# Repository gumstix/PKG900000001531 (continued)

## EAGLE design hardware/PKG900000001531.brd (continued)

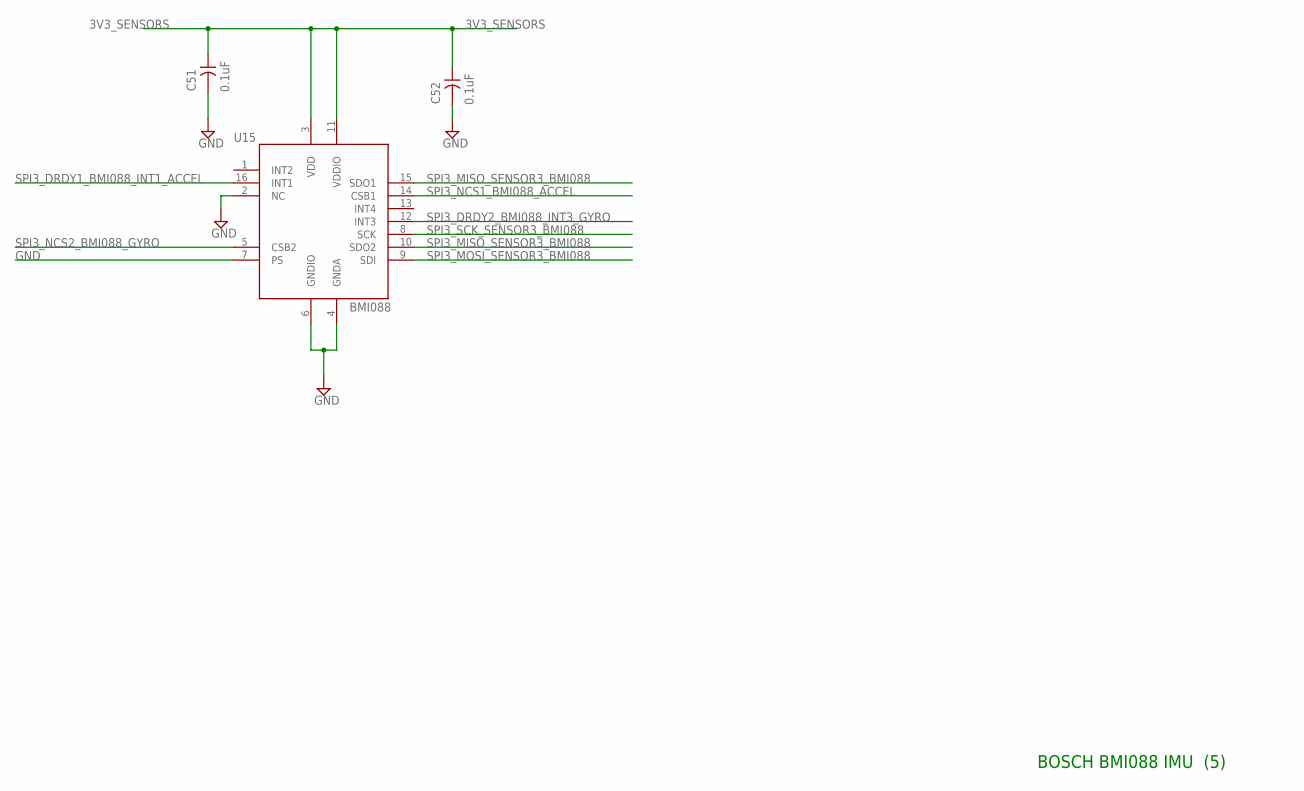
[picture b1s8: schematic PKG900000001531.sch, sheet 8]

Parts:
C51, C52: 0.1uF; 0201
U15: BMI088; LGA16-BMI088

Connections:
3V3_SENSORS: C51.1, C52.1, U15.3 (VDD), U15.11 (VDDIO); also elsewhere on the board
GND: C51.2, C52.2, U15.2 (NC), U15.4 (GNDA), U15.6 (GNDIO), U15.7 (PS); also elsewhere on the board
SPI3_DRDY1_BMI088_INT1_ACCEL: U15.16 (INT1); also elsewhere on the board
SPI3_DRDY2_BMI088_INT3_GYRO: U15.12 (INT3); also elsewhere on the board
SPI3_MISO_SENSOR3_BMI088: U15.10 (SDO2), U15.15 (SDO1); also elsewhere on the board
SPI3_MOSI_SENSOR3_BMI088: U15.9 (SDI); also elsewhere on the board
SPI3_NCS1_BMI088_ACCEL: U15.14 (CSB1); also elsewhere on the board
SPI3_NCS2_BMI088_GYRO: U15.5 (CSB2); also elsewhere on the board
SPI3_SCK_SENSOR3_BMI088: U15.8 (SCK); also elsewhere on the board

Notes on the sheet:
BOSCH BMI088 IMU (5)

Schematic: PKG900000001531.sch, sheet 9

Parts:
C53, C55: 0.1uF; 0201
R13, R47, R77: 10K 1%; 0201
R17, R46, R86, R87, R88: DNP; 0201
R90, R107: 0R; 0201
R108, R109: 1K5; 0201
U9: BMM150; WLCSP-12

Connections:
3V3_SENSORS: C53.1, C55.1, R47.2, R108.1, R109.1, U9.B2 (VDDIO), U9.E5 (VDD); also elsewhere on the board
BMM150_PS: R46.2, R47.1, U9.A1 (PS)
CSB$1: R77.2, R87.2, U9.A5 (CSB)
GND: C53.2, C55.2, R13.1, R46.1, R77.1, U9.C5 (GND), U9.E1 (GND), U9.E3 (GND); also elsewhere on the board
I2C4_SCL_FMU: R107.2, R109.2; also elsewhere on the board
I2C4_SDA_FMU: R90.2, R108.2; also elsewhere on the board
SCK$1: R17.1, R107.1, U9.A3 (SCK)
SDI$1: R88.1, R90.1, U9.B4 (SDI)
SDO$1: R13.2, R86.2, U9.C1 (SDO)
SPI4_DRDY1_BMM150_DRDY: U9.D4 (DRDY); also elsewhere on the board
SPI4_MISO_SENSOR4_BMM150: R86.1; also elsewhere on the board
SPI4_MOSI_SENSOR4_BMM150: R88.2; also elsewhere on the board
SPI4_NCS1_BMM150: R87.1; also elsewhere on the board
SPI4_SCK_SENSOR4_BMM150: R17.2; also elsewhere on the board

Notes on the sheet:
Bosch BMM150 Magnetometer (6)

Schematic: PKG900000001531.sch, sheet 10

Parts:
C54: DNP; 0201
C70, C71: 0.1uF; 0201
R51, R53, R57, R59: DNP; 0201
U10: DNP; BA03
U108: BMP388; LGA10

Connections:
3V3_SENSORS: C54.1, C70.1, C71.1, R53.1, R57.1, R59.2, U10.1 (VDD), U108.1 (VDDIO), U108.6 (CSB), U108.10 (VDD); also elsewhere on the board
GND: C54.2, C70.2, C71.2, R51.1, U10.3 (GND), U108.3 (VSS), U108.5 (SDO), U108.8 (VSS), U108.9 (VSS); also elsewhere on the board
I2C2_DRDY1_BMP388: U108.7 (INT); also elsewhere on the board
I2C3_SCL_BASE_MS5611_BARBED_EXTERNAL1: R57.2, U10.8 (SCLK); also elsewhere on the board
I2C3_SDA_BASE_MS5611_BARBED_EXTERNAL1: R53.2, U10.7 (SDA); also elsewhere on the board
I2C4_SCL_FMU: U108.2 (SCK); also elsewhere on the board
I2C4_SDA_FMU: U108.4 (SDI); also elsewhere on the board
MS5611_CS$1: R51.2, U10.4 (CSB)
MS5611_PS$1: R59.1, U10.2 (PS)

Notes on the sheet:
BMP388 & MS5611 Barometer (7)

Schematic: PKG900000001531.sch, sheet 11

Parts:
D2: EAST1616RGBB4; SMD4
R78: 196R; 0201
R79, R85: 100R; 0201

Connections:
2.3.3V_VCC_3.3: D2.4 (VCC); also elsewhere on the board
C_BLUE$1: D2.3 (B), R85.1
C_GREEN$1: D2.2 (G), R79.1
C_RED$1: D2.1 (R), R78.1
NLED_BLUE: R85.2; also elsewhere on the board
NLED_GREEN: R79.2; also elsewhere on the board
NLED_RED: R78.2; also elsewhere on the board

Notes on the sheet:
Discrete RGB LED (16)

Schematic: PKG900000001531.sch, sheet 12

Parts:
C228: 0.1uF / 16V; 0402
C230: 10uF / 16V; 0805
C231: 1.0uF; 0402
C232: 10pF; 0201
C233: 22uF; 0805
IC3: TPS62111; PQFP16
L1: 6.8uH; 1515
R80: 1M0; 0201
R81: 0R; 0402
R83: DNP; 0402

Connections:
2.3.3V_VCC_3.3: C232.1, C233.1, L1.2, R80.2, R81.2; also elsewhere on the board
14.5.0V_VCC_5.0: C228.1, C230.1, C231.1, IC3.2 (VIN), IC3.3 (VIN), IC3.4 (EN), IC3.8 (VIN); also elsewhere on the board
FB_3.3$2: C232.2, IC3.10 (FB), R81.1, R83.2
GND: C228.2, C230.2, C231.2, C233.2, IC3.1 (PGND), IC3.5 (SYNC), IC3.6 (LBO), IC3.7 (LBI), IC3.9 (GND), IC3.11 (GND), IC3.12 (GND), IC3.16 (PGND), IC3.P$1 (GND), R83.1; also elsewhere on the board
PG_3.3$2: IC3.13 (PG), R80.1
SW_3.3$2: IC3.14 (SW), IC3.15 (SW), L1.1

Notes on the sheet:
3.3V 1500mA Buck

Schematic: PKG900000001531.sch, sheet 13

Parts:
C226: 1.0uF; 0402
J7: USB-TYPE-C; USB-TYPE-C-SMT
L9: DLP11SN900HL2; 0504-DLP11S
R68, R89: 5K1; 0201
R82: 0R; 0201
U107: TPD4E02B0410-USON; UFDFN-10

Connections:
3.5.0V_VCC_5.0: C226.1, J7.A4 (VBUS), J7.A9 (VBUS), J7.B4 (VBUS), J7.B9 (VBUS), R82.2, U107.5 (P4), U107.6 (P4); also elsewhere on the board
4.USB_D_N: L9.3; also elsewhere on the board
4.USB_D_P: L9.2; also elsewhere on the board
CC1$3: J7.A5 (CC1), R68.2
CC2$3: J7.B5 (CC2), R89.2
COMMON_SHIELD: J7.P$1 (SHIELD), J7.P$2 (SHIELD), J7.P$3 (SHIELD), J7.P$4 (SHIELD), U107.3 (SHIELD), U107.8 (SHIELD)
D_N$3: J7.A7 (D-), J7.B7 (D-), L9.4, U107.1, U107.10 (P1)
D_P$3: J7.A6 (D+), J7.B6 (D+), L9.1, U107.2, U107.9 (P2)
GND: C226.2, J7.A1 (GND), J7.A12 (GND), J7.B1 (GND), J7.B12 (GND), R68.1, R89.1; also elsewhere on the board
RX1_N$3: J7.B10 (RX1-)
RX1_P$3: J7.B11 (RX1+)
RX2_N$3: J7.A10 (RX2-)
RX2_P$3: J7.A11 (RX2+)
TX1_N$3: J7.A3 (TX1-)
TX1_P$3: J7.A2 (TX1+)
TX2_N$3: J7.B3 (TX2-)
TX2_P$3: J7.B2 (TX2+)
VBUS_SENSE: R82.1; also elsewhere on the board

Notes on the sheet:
USB Type-C PD (5V)
Pull both CC pins low with 5.1K 1% to enable UFP and PD.

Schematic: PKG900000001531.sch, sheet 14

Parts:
C7, C13, C95, C97, C238, C239, C240, C241, C248: 0.1uF; 0201
C8, C31, C96: 1.0uF; 0402
C9: 4.7uF; 0603
C10, C11: 22pF; 0201
C12: 0.1uF; 0402
R5, R91, R92, R93, R97, R98, R99: 100K 1%; 0201
R96: 1M0; 0201
R102: 12K0; 0201
U14: USB2517-JZX; QFN64-9X9MM-FT2232HQ
Y1: 24.000MHz; CRYSTAL-3225

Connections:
1.USB_HS_D_N: U14.1 (USBDN1_DM/PRT_DIS_M1); also elsewhere on the board
1.USB_HS_D_P: U14.2 (USBDN1_DP/PRT_DIS_P1); also elsewhere on the board
2.3.3V_VCC_3.3: C7.1, C8.1, C9.1, C13.1, C238.1, C239.1, C240.1, C241.1, C248.1, R5.1, R91.1, R97.1, R98.2, U14.5 (VDDA33_2), U14.10 (VDDA33_4), U14.24 (VDD33CR), U14.46 (VDD33), U14.52 (VDDA33_3), U14.57 (VDDA33), U14.64 (VDD33PLL); also elsewhere on the board
4.USB_D_N: U14.58 (USBUP_DM); also elsewhere on the board
4.USB_D_P: U14.59 (USBUP_DP); also elsewhere on the board
5.USB_DEVICE_D_N: U14.53 (USBDN6_DM/PRT_DIS_M6); also elsewhere on the board
5.USB_DEVICE_D_P: U14.54 (USBDN6_DP/PRT_DIS_P6); also elsewhere on the board
6.USB_DEVICE_D_N: U14.55 (USBDN7_DM/PRT_DIS_M7); also elsewhere on the board
6.USB_DEVICE_D_P: U14.56 (USBDN7_DP/PRT_DIS_P7); also elsewhere on the board
CFG_SEL2$: R5.2, U14.13 (CFG_SEL2)
CORAL_D_N: U14.11 (USBDN5_DM/PRT_DIS_M5); also elsewhere on the board
CORAL_D_P: U14.12 (USBDN5_DP/PRT_DIS_P5); also elsewhere on the board
GND: C7.2, C8.2, C9.2, C10.2, C11.2, C12.2, C13.2, C31.2, C95.2, C96.2, C97.2, C238.2, C239.2, C240.2, C241.2, C248.2, R92.1, R93.1, R99.1, R102.1, U14.19 (TEST), U14.65 (EPAD), U14.EPAD1 (EPAD), U14.EPAD2 (EPAD), U14.EPAD3 (EPAD), U14.EPAD4 (EPAD), U14.EPAD5 (EPAD), U14.EPAD6 (EPAD), U14.EPAD7 (EPAD), U14.EPAD8 (EPAD), U14.EPAD9 (EPAD), U14.EPAD10 (EPAD), U14.EPAD11 (EPAD), U14.EPAD12 (EPAD), Y1.2, Y1.4; also elsewhere on the board
USB_CRFILT$: C31.1, C95.1, U14.25 (VDD18)
USB_D_N: U14.3 (USBDN2_DM/PRT_DIS_M2); also elsewhere on the board
USB_D_P: U14.4 (USBDN2_DP/PRT_DIS_P2); also elsewhere on the board
USB_HS_IND$4: R91.2, U14.42 (HS_IND/CFG_SEL1)
USB_NRESET$4: C12.1, R98.1, U14.43 (RESET_N)
USB_PLLFILT$: C96.1, C97.1, U14.62 (VDD18PLL)
USB_RBIAS$4: R102.2, U14.63 (RBIAS)
USB_SCL$4: R99.2, U14.41 (SCL/SMBCLK/CFG_SEL0)
USB_SDA$4: R93.2, U14.40 (SDA/SMBDATA/NON_REM1)
USB_SUSP_IND$4: R92.2, U14.45 (SUSP_IND/LOCAL_PWR/NON_REM0)
USB_XTAL1$4: C11.1, R96.2, U14.61 (XTAL1/CLKIN), Y1.3
USB_XTAL2$4: C10.1, R96.1, U14.60 (XTAL2), Y1.1
VBUS_DET$: R97.2, U14.44 (VBUS_DET)

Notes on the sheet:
7-Port USB Client Hub

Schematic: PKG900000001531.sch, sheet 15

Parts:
C243, C244, C245, C247: 0.1uF; 0201
C246: 4.7uF; 0603
FB4: 120R 1A; 0402
IC5: FT232RQ; QFN32
IC6: SN74LVC1G126DCKR; SC70-5
R55, R56: 10K 1%; 0201
U30: TS3A5223; UQFN-10

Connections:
2.3.3V_VCC_3.3: C243.1, C247.1, IC5.1 (VCCIO), IC6.1 (OE), IC6.5 (VCC), U30.1 (VCC); also elsewhere on the board
5.USB_DEVICE_D_N: IC5.15 (USBDM); also elsewhere on the board
5.USB_DEVICE_D_P: IC5.14 (USBDP); also elsewhere on the board
FTDI_3.3_INT$5: C244.1, IC5.16 (3V3OUT)
GND: C243.2, C244.2, C245.2, C246.2, C247.2, IC5.4 (GND), IC5.17 (GND), IC5.20 (GND), IC5.24 (GND), IC5.26 (TEST), IC6.3 (GND), R56.1, U30.6 (GND); also elsewhere on the board
RX_SW$5: IC5.30 (TXD), IC6.2 (I)
UART_MUX_SEL$: R55.1, R56.2, U30.4 (SEL1), U30.8 (SEL2)
USART3_RX_DEBUG: U30.3 (COM1); also elsewhere on the board
USART3_RX_DEBUG_FTDI: IC6.4 (O), U30.2 (NO1)
USART3_RX_DEBUG_JST: U30.5 (NC1); also elsewhere on the board
USART3_TX_DEBUG: U30.9 (COM2); also elsewhere on the board
USART3_TX_DEBUG_FTDI: IC5.2 (RXD), U30.10 (NO2)
USART3_TX_DEBUG_JST: U30.7 (NC2); also elsewhere on the board
VBUS$5: C245.1, C246.1, FB4.2, IC5.18 (!RESET), IC5.19 (VCC)
VBUS_SENSE: FB4.1, R55.2; also elsewhere on the board

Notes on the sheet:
USB to UART

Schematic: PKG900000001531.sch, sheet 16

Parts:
C4, C5, C249, C253: 0.1uF; 0201
C250: 4.7uF; 0603
FB1: 120R 1A; 0402
IC2: FT232RQ; QFN32
IC7: SN74LVC1G126DCKR; SC70-5

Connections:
6.USB_DEVICE_D_N: IC2.15 (USBDM); also elsewhere on the board
6.USB_DEVICE_D_P: IC2.14 (USBDP); also elsewhere on the board
7.UART0_RXD: IC7.4 (O); also elsewhere on the board
7.UART0_TXD: IC2.2 (RXD); also elsewhere on the board
7.VLOGIC_VLOGIC: C4.1, C249.1, IC2.1 (VCCIO), IC7.1 (OE), IC7.5 (VCC); also elsewhere on the board
FTDI_3.3_INT$6: C5.1, IC2.16 (3V3OUT)
GND: C4.2, C5.2, C249.2, C250.2, C253.2, IC2.4 (GND), IC2.17 (GND), IC2.20 (GND), IC2.24 (GND), IC2.26 (TEST), IC7.3 (GND); also elsewhere on the board
RX_SW$6: IC2.30 (TXD), IC7.2 (I)
VBUS$6: C250.1, C253.1, FB1.2, IC2.18 (!RESET), IC2.19 (VCC)
VBUS_SENSE: FB1.1; also elsewhere on the board

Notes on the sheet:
USB to UART

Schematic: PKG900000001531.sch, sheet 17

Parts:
J2, J8: DF40HC(3.0)-100DS-0.4V(51); HRS_DF40C-100DS-0.4V(51)
MP1, MP2, MP3, MP4: 9774030151R; WA-SMSI_9774___151
Q1, Q3, Q4, Q6: FDN360P; SOT23
Q5: BSS138; SOT23
R9, R42, R101, R113: 0R; 0201
R103: 10K 1%; 0201
R106: DNP; 0201

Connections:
1.8V_OUT$7: J8.88, J8.90, Q1.3 (D), R106.1
3.3V_OUT$7: J8.84, J8.86, Q4.3 (D), R101.1
7.1.8V_VCC_1.8: Q6.3 (D); also elsewhere on the board
7.3.3V_VCC_3.3: Q3.3 (D), R113.2; also elsewhere on the board
7.CAM0_C_N: J2.40; also elsewhere on the board
7.CAM0_C_P: J2.42; also elsewhere on the board
7.CAM0_D1_N: J2.28; also elsewhere on the board
7.CAM0_D1_P: J2.30; also elsewhere on the board
7.CAM0_D2_N: J2.34; also elsewhere on the board
7.CAM0_D2_P: J2.36; also elsewhere on the board
7.CAM1_C_N: J2.27; also elsewhere on the board
7.CAM1_C_P: J2.29; also elsewhere on the board
7.CAM1_D1_N: J2.15; also elsewhere on the board
7.CAM1_D1_P: J2.17; also elsewhere on the board
7.CAM1_D2_N: J2.21; also elsewhere on the board
7.CAM1_D2_P: J2.23; also elsewhere on the board
7.CAM1_D3_N: J2.33
7.CAM1_D3_P: J2.35
7.CAM1_D4_N: J2.39
7.CAM1_D4_P: J2.41
7.GPIO2_GPIO: J8.58; also elsewhere on the board
7.GPIO3_GPIO: J8.56; also elsewhere on the board
7.GPIO4_GPIO: J8.54; also elsewhere on the board
7.GPIO5_GPIO: J8.34; also elsewhere on the board
7.GPIO6_GPIO: J8.30; also elsewhere on the board
7.GPIO7_GPIO: J8.37; also elsewhere on the board
7.I2C0_SCL: J8.80; also elsewhere on the board
7.I2C0_SDA: J8.82; also elsewhere on the board
7.I2C_ID_SCL: J8.35; also elsewhere on the board
7.I2C_ID_SDA: J8.36; also elsewhere on the board
7.PCIE_CLKREQ_GPIO: J2.2, R9.1
7.PCIE_NRESET: J2.9; also elsewhere on the board
7.UART0_RXD: J8.51; also elsewhere on the board
7.UART0_TXD: J8.55; also elsewhere on the board
7.UART4_4W_CTS: J8.44; also elsewhere on the board
7.UART4_4W_RTS: J8.38; also elsewhere on the board
7.UART4_4W_RXD: J8.40; also elsewhere on the board
7.UART4_4W_TXD: J8.39; also elsewhere on the board
7.VLOGIC_VLOGIC: R113.1; also elsewhere on the board
14.5.0V_VCC_5.0: J8.77, J8.79, J8.81, J8.83, J8.85, J8.87; also elsewhere on the board
!EXTRST$7: J8.100, Q5.1 (G), R103.2
!RPIBOOT$7: J8.93; also elsewhere on the board
CORAL_D_N: J2.3; also elsewhere on the board
CORAL_D_P: J2.5; also elsewhere on the board
DS_LOAD$7: Q3.2 (S), Q4.2 (S)
DS_LOAD_1V8$7: Q1.2 (S), Q6.2 (S)
EEPROM_!WP: J8.20
ETH_SYNC_IN: J8.16
ETH_SYNC_OUT: J8.18
GLOBAL_EN: J8.99
GND: J2.7, J2.8, J2.13, J2.14, J2.19, J2.20, J2.25, J2.26, J2.31, J2.32, J2.37, J2.38, J2.44, J2.50, J2.55, J2.56, J2.61, J2.62, J2.67, J2.68, J2.73, J2.74, J2.79, J2.80, J2.85, J2.86, J2.91, J2.92, J2.97, J2.98, J8.1, J8.2, J8.7, J8.8, J8.13, J8.14, J8.22, J8.23, J8.32, J8.33, J8.42, J8.43, J8.52, J8.53, J8.59, J8.60, J8.65, J8.66, J8.71, J8.74, J8.98, MP1.1, MP2.1, MP3.1, MP4.1, Q5.2 (S), R9.2, R42.2, R103.1; also elsewhere on the board
GPIO_VREF$7: J8.78, R101.2, R106.2; also elsewhere on the board
LOAD_GATE$7: Q1.1 (G), Q3.1 (G), Q4.1 (G), Q5.3 (D), Q6.1 (G)
PCIE_CLK_N: J2.12; also elsewhere on the board
PCIE_CLK_P: J2.10; also elsewhere on the board
PCIE_RX_N: J2.18; also elsewhere on the board
PCIE_RX_P: J2.16; also elsewhere on the board
PCIE_TX_N: J2.24; also elsewhere on the board
PCIE_TX_P: J2.22; also elsewhere on the board
PI_!LED_ACT: J8.21
PI_LED_!PWR: J8.95
SD_PWR_ON: J8.75
SD_VDD_OV: J8.73
USB_OTG_ID: J2.1, R42.1
VDAC_COMP: J2.11

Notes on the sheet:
Raspberry Pi CM4
GPIO
High Speed

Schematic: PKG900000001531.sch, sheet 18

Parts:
C6: 0.1uF; 0201
IC1: CAT24C256YI-G; TSSOP8
R8, R104, R105: 100K 1%; 0201
R10, R20, R110: 1K5; 0201
S2: EVQ; KMT0

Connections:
7.I2C_ID_SCL: IC1.6 (SCL), R10.1; also elsewhere on the board
7.I2C_ID_SDA: IC1.5 (SDA), R110.1; also elsewhere on the board
!RPIBOOT$7: S2.3 (B), S2.4 (B'); also elsewhere on the board
A0$7: IC1.1 (A0), R8.2
A1$7: IC1.2 (A1), R105.2
A2$7: IC1.3 (A2), R104.2
GND: C6.2, IC1.4 (GND), IC1.7 (WP), R20.1, R104.1, R105.1; also elsewhere on the board
GPIO_VREF$7: C6.1, IC1.8 (VCC), R8.1, R10.2, R110.2; also elsewhere on the board
RPIBOOT_SWITCH$19: R20.2, S2.1 (A), S2.2 (A')

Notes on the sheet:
Raspberry Pi CM4

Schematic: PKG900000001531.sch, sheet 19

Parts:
R1, R3, R52, R54: 0R; 0201
R2, R4: DNP; 0201

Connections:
7.UART4_4W_CTS: R2.1, R3.1; also elsewhere on the board
7.UART4_4W_RTS: R1.1, R4.1; also elsewhere on the board
7.UART4_4W_RXD: R54.1; also elsewhere on the board
7.UART4_4W_TXD: R52.1; also elsewhere on the board
UART5_CTS_TELEM2: R1.2, R2.2; also elsewhere on the board
UART5_RTS_TELEM2: R3.2, R4.2; also elsewhere on the board
UART5_RX_TELEM2: R52.2; also elsewhere on the board
UART5_TX_TELEM2: R54.2; also elsewhere on the board

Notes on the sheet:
HART-HART Bridge

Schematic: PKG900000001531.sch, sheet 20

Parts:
J9: CON8X3STD; MA08-3W-0100
R29, R30, R32, R33, R34, R35, R36, R37: 220R; 0402
U17, U18: TPD4E02B0410-USON; UFDFN-10

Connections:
1.PWM1_PWM_: J9.17, R29.2
1.PWM2_PWM_: J9.18, R30.2
1.PWM3_PWM_: J9.19, R32.2
1.PWM4_PWM_: J9.20, R33.2
1.PWM5_PWM_: J9.21, R34.2
1.PWM6_PWM_: J9.22, R35.2
1.PWM7_PWM_: J9.23, R36.2
1.PWM8_PWM_: J9.24, R37.2
5V_HIGH: J9.9, J9.10, J9.11, J9.12, J9.13, J9.14, J9.15, J9.16; also elsewhere on the board
FMU_CH1: R29.1, U18.5 (P4), U18.6 (P4); also elsewhere on the board
FMU_CH2: R30.1, U18.4 (P3), U18.7 (P3); also elsewhere on the board
FMU_CH3: R32.1, U18.2, U18.9 (P2); also elsewhere on the board
FMU_CH4: R33.1, U18.1, U18.10 (P1); also elsewhere on the board
FMU_CH5: R34.1, U17.5 (P4), U17.6 (P4); also elsewhere on the board
FMU_CH6: R35.1, U17.4 (P3), U17.7 (P3); also elsewhere on the board
FMU_CH7: R36.1, U17.2, U17.9 (P2); also elsewhere on the board
FMU_CH8: R37.1, U17.1, U17.10 (P1); also elsewhere on the board
GND: J9.1, J9.2, J9.3, J9.4, J9.5, J9.6, J9.7, J9.8, U17.3 (SHIELD), U17.8 (SHIELD), U18.3 (SHIELD), U18.8 (SHIELD); also elsewhere on the board

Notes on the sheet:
Octal Servo

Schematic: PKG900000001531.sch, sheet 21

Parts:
J10: FPC-15VERT; 1-1734248-5

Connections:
2.3.3V_VCC_3.3: J10.1_15 (15); also elsewhere on the board
7.CAM0_C_N: J10.1_8 (8); also elsewhere on the board
7.CAM0_C_P: J10.1_9 (9); also elsewhere on the board
7.CAM0_D1_N: J10.1_2 (2); also elsewhere on the board
7.CAM0_D1_P: J10.1_3 (3); also elsewhere on the board
7.CAM0_D2_N: J10.1_5 (5); also elsewhere on the board
7.CAM0_D2_P: J10.1_6 (6); also elsewhere on the board
7.GPIO4_GPIO: J10.1_11 (11); also elsewhere on the board
7.I2C_ID_SCL: J10.1_13 (13); also elsewhere on the board
7.I2C_ID_SDA: J10.1_14 (14); also elsewhere on the board
GND: J10.1_1 (1), J10.1_4 (4), J10.1_7 (7), J10.1_10 (10); also elsewhere on the board

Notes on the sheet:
RPi CSI Vertical Connector

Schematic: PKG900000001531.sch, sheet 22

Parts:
J11: FPC-15VERT; 1-1734248-5

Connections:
2.3.3V_VCC_3.3: J11.1_15 (15); also elsewhere on the board
7.CAM1_C_N: J11.1_8 (8); also elsewhere on the board
7.CAM1_C_P: J11.1_9 (9); also elsewhere on the board
7.CAM1_D1_N: J11.1_2 (2); also elsewhere on the board
7.CAM1_D1_P: J11.1_3 (3); also elsewhere on the board
7.CAM1_D2_N: J11.1_5 (5); also elsewhere on the board
7.CAM1_D2_P: J11.1_6 (6); also elsewhere on the board
7.GPIO5_GPIO: J11.1_11 (11); also elsewhere on the board
7.I2C0_SCL: J11.1_13 (13); also elsewhere on the board
7.I2C0_SDA: J11.1_14 (14); also elsewhere on the board
GND: J11.1_1 (1), J11.1_4 (4), J11.1_7 (7), J11.1_10 (10); also elsewhere on the board

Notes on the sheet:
RPi CSI Vertical Connector

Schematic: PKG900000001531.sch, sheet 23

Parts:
J12: JST-GH-6H

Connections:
5V_PERIPHERAL: J12.P1; also elsewhere on the board
GND: J12.P6; also elsewhere on the board
I2C1_SCL_BASE_GPS1_MAG_LED_PM1: J12.P4; also elsewhere on the board
I2C1_SDA_BASE_GPS1_MAG_LED_PM1: J12.P5; also elsewhere on the board
USART1_RX_GPS1: J12.P3; also elsewhere on the board
USART1_TX_GPS1: J12.P2; also elsewhere on the board

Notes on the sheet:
JST GH 6-pin (GPS) Header

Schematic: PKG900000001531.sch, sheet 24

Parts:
J13: JST-GH-6H

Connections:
13.VCC_VCC_5.0: J13.P1, J13.P2; also elsewhere on the board
ADC3_3V3: J13.P4; also elsewhere on the board
ADC3_6V6: J13.P3; also elsewhere on the board
GND: J13.P5, J13.P6; also elsewhere on the board

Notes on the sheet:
JST GH 6-pin (Power) Header

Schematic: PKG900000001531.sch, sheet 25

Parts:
C270: 0.01uF; 0201
R6, R111: 24K; 0201
R7: 22K; 0201
R112: 0R; 0201
R114, R115: 5K; 0201
U105: TPS2121; VQFN12-HR

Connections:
3.5.0V_VCC_5.0: R111.2, U105.7 (IN1); also elsewhere on the board
13.VCC_VCC_5.0: R6.2, U105.2 (IN2); also elsewhere on the board
14.5.0V_VCC_5.0: U105.1 (OUT), U105.8 (OUT); also elsewhere on the board
GND: C270.2, R7.1, R112.1, R114.1, R115.1, U105.3 (CP2), U105.9 (ST), U105.12 (GND); also elsewhere on the board
ILUM$14: R7.2, U105.10 (ILM)
OV1$14: R111.1, R114.2, U105.5 (OV1)
OV2$14: R6.1, R115.2, U105.4 (OV2)
PR1$14: R112.2, U105.6 (PR1)
SS$14: C270.1, U105.11 (SS)

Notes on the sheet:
TI TPS2121 Power Source Muxer

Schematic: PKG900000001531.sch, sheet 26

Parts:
J14: JST-GH-4H

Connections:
5V_PERIPHERAL: J14.P1; also elsewhere on the board
18.CAN_HL_CAN_H: J14.P2; also elsewhere on the board
18.CAN_HL_CAN_L: J14.P3; also elsewhere on the board
GND: J14.P4; also elsewhere on the board

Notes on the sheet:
JST GH 4-pin (CAN) Header

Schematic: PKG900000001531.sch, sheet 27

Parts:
J1: JST-GH-5H

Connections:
3V3_SPEKTRUM: J1.P4; also elsewhere on the board
5V_PERIPHERAL: J1.P1; also elsewhere on the board
FMU_PPM_INPUT: J1.P3; also elsewhere on the board
GND: J1.P5; also elsewhere on the board
USART6_RX_FROM_IO__RC_INPUT: J1.P2; also elsewhere on the board

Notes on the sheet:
JST GH 5-pin (RC) Header

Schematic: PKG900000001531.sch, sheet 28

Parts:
C16, C27, C34, C38, C72: 0.1uF; 0201
C28: 10uF; 0603
C40: 1000pF; 0201
C41: 270pF; 0201
R19, R43, R58: 0R; 0201
R21, R48: 10K 1%; 0201
R27, R28: 1K5; 0201
R49: 14K7; 0201
R50: 100K 1%; 0201
U5: G313-06329-00
U6: NCP308; WDFN6
U19: TXS0104E; S-PVQFN-N14

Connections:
7.1.8V_VCC_1.8: C34.1, R19.2, R21.2, R27.2, R28.2, R48.2, U5.54 (AON), U19.1 (VCCA), U19.8 (OE); also elsewhere on the board
7.3.3V_VCC_3.3: C27.1, C28.1, C38.1, R50.2, U5.56 (VIN), U5.57 (VIN), U5.58 (VIN), U5.59 (VIN), U5.60 (VIN), U5.61 (VIN), U5.62 (VIN), U5.63 (VIN), U5.64 (VIN), U5.65 (VIN), U5.66 (VIN), U5.67 (VIN), U6.1 (VDD), U19.14 (VCCB); also elsewhere on the board
7.GPIO2_GPIO: U19.11 (B3); also elsewhere on the board
7.GPIO3_GPIO: U19.10 (B4); also elsewhere on the board
7.GPIO6_GPIO: U19.12 (B2); also elsewhere on the board
7.GPIO7_GPIO: U19.13 (B1); also elsewhere on the board
!RST$17: R48.1, U5.76 (!RST), U6.6 (!RESET)
CT1$17: C41.1, U6.3 (CT)
GND: C27.2, C28.2, C34.2, C38.2, C40.2, C41.2, R43.1, R49.1, R58.1, U5.1 (GND), U5.2 (GND), U5.3 (GND), U5.6 (GND), U5.9 (GND), U5.12 (GND), U5.15 (GND), U5.16 (GND), U5.17 (GND), U5.18 (GND), U5.19 (GND), U5.20 (GND), U5.21 (GND), U5.22 (GND), U5.23 (GND), U5.24 (GND), U5.25 (GND), U5.26 (GND), U5.27 (GND), U5.28 (GND), U5.29 (GND), U5.30 (GND), U5.31 (GND), U5.32 (GND), U5.33 (GND), U5.34 (GND), U5.35 (GND), U5.36 (GND), U5.38 (GND), U5.39 (GND), U5.40 (GND), U5.41 (GND), U5.42 (GND), U5.43 (GND), U5.44 (GND), U5.45 (GND), U5.46 (GND), U5.47 (GND), U5.48 (GND), U5.51 (GND), U5.55 (GND), U5.68 (GND), U5.69 (GND), U5.70 (GND), U5.71 (GND), U5.72 (GND), U5.73 (GND), U5.74 (GND), U5.75 (GND), U5.79 (GND), U5.80 (GND), U5.81 (GND), U5.86 (GND), U5.87 (GND), U5.88 (GND), U5.89 (GND), U5.90 (GND), U5.91 (GND), U5.92 (GND), U5.93 (GND), U5.94 (GND), U5.95 (GND), U5.96 (GND), U5.97 (GND), U5.98 (GND), U5.99 (GND), U5.100 (GND), U5.101 (GND), U5.102 (GND), U5.103 (GND), U5.104 (GND), U5.105 (GND), U5.106 (GND), U5.107 (GND), U5.108 (GND), U5.109 (GND), U5.110 (GND), U5.111 (GND), U5.112 (GND), U5.113 (GND), U5.114 (GND), U5.115 (GND), U5.116 (GND), U5.117 (GND), U5.118 (GND), U5.119 (GND), U5.120 (GND), U6.5 (GND), U6.EPAD (GND), U19.7 (GND); also elsewhere on the board
I2C_SCL: R27.1, U5.50 (RESERVED), U19.5 (A4)
I2C_SDA: R28.1, U5.49 (RESERVED), U19.4 (A3)
PGOOD4$17: U5.37 (PGOOD4), U6.4 (!MR)
PHY_PRG: U5.84 (RESERVED), U19.2 (A1)
PMIC_EN$17: R21.1, U5.53 (PMIC_EN), U19.3 (A2)
SD_ALRM$17: U5.82 (SD_ALRM)
SENSE$17: C40.1, R49.2, R50.1, U6.2 (SENSE)
USB1_N: U5.14 (USB2_D_N); also elsewhere on the board
USB1_P: U5.13 (USB2_D_P); also elsewhere on the board
USB1_SSRX_N: U5.4 (PCIE_TX_N); also elsewhere on the board
USB1_SSRX_P: U5.5 (PCIE_TX_P); also elsewhere on the board
USB1_SSTX_N: C16.2; also elsewhere on the board
USB1_SSTX_P: C72.2; also elsewhere on the board
USB1_SSTX__N: C16.1, U5.7 (PCIE_RX_P)
USB1_SSTX__P: C72.1, U5.8 (PCIE_RX_N)
USB_SEL$17: R19.1, U5.83 (USB_SEL)
_PCIE_CLK_N: R43.2, U5.10 (PCIE_REFCLK_N)
_PCIE_CLK_P: R58.2, U5.11 (PCIE_REFCLK_P)

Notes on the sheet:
Google Coral G313-06329-00 Accelerator

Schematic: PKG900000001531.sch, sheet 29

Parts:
C2: 4.7nF; 0201
C3, C271: 0.1uF; 0201
R117: 10K 1%; 0201
RT4, RT5: 60R4; 0805
U2: TJA1051TK/3; HVSON8

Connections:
2.3.3V_VCC_3.3: C3.1, U2.5 (VIO); also elsewhere on the board
5V_PERIPHERAL: C271.1, U2.3 (VCC); also elsewhere on the board
18.CAN_HL_CAN_H: RT4.2, U2.7 (CANH); also elsewhere on the board
18.CAN_HL_CAN_L: RT5.1, U2.6 (CANL); also elsewhere on the board
CAN1_RX: U2.4 (RXD); also elsewhere on the board
CAN1_TX: U2.1 (TXD); also elsewhere on the board
CAP$18: C2.1, RT4.1, RT5.2
GND: C2.2, C3.2, C271.2, R117.1, U2.2 (GND), U2.P$1 (FLAG), U2.P$2 (FLAG), U2.P$3 (FLAG), U2.P$4 (FLAG), U2.P$5 (FLAG), U2.P$6 (FLAG), U2.P$8 (FLAG), U2.P$9 (FLAG); also elsewhere on the board
SEL$18: R117.2, U2.8 (S)

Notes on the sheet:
NXP TJA1051TK/3 CAN Transceiver

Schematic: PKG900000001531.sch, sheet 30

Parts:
C1: 47pF; 0201
D1: B72590D50A060; D0402
R119: 10K 1%; 0201
R120: 150R; 0201
S1: EVQ

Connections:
2.3.3V_VCC_3.3: R119.2; also elsewhere on the board
BTN_A$22: D1.P2, R119.1, R120.1, S1.B@1 (B), S1.B@2 (B')
GND: C1.2, D1.P1, S1.A@1 (A), S1.A@2 (A'); also elsewhere on the board
NRST: C1.1, R120.2; also elsewhere on the board

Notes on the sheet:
Pushbutton

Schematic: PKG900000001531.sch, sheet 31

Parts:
C14: 0.1uF; 0201
C15: 10uF; 0603
J3: USD_WURTH; USD
RP2: 33R0; 741X16
RP3: 100K0; 741X16

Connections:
1.SD_CARD_POWER: C14.1, C15.1, J3.4 (VDD), RP3.1, RP3.2, RP3.3, RP3.4, RP3.5, RP3.6; also elsewhere on the board
3V_MMC_CLK$24: J3.5 (CLK/SCLK), RP2.15
3V_MMC_CMD$24: J3.3 (CMD/DI), RP2.16
3V_MMC_D0$24: J3.7 (DAT0/DO), RP2.14
3V_MMC_D1$24: J3.8 (DAT1/RSV), RP2.13
3V_MMC_D2$24: J3.1 (DAT2/RSV), RP2.12
3V_MMC_D3$24: J3.2 (DAT3_CD/CS), RP2.11
GND: C14.2, C15.2, J3.6 (GND); also elsewhere on the board
SDMMC2_CLK: RP2.2; also elsewhere on the board
SDMMC2_CMD: RP2.1, RP3.16; also elsewhere on the board
SDMMC2_D0: RP2.3, RP3.14; also elsewhere on the board
SDMMC2_D1: RP2.4, RP3.13; also elsewhere on the board
SDMMC2_D2: RP2.5, RP3.12; also elsewhere on the board
SDMMC2_D3: RP2.6, RP3.11; also elsewhere on the board

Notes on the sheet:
SD Card

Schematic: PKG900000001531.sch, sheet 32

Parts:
C32: 10pF; 0201
C73, C74, C75, C76, C77, C78, C79, C82, C83, C84, C85, C86, C88, C89, C92, C93: 0.1uF; 0201
C90, C91: 4.7uF / 16V; 0603
C94: 6.8nF; 0201
C158, C167: 10uF; 0603
R11: 12K1; 0201
R69, R70: 10K 1%; 0201
U4: ASM1142; QFN64-9X9MM-FT2232HQ
U12: ADP1740ACPZ-1.2-R7; LFCSPWQ16
Y5: 20.000MHz; CRYSTAL-3225

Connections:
2.3.3V_VCC_3.3: C73.1, C76.1, C77.1, C85.1, C86.1, C88.1, C158.1, R69.2, R70.2, U4.4 (VCC), U4.20 (VCCSUS), U4.24 (VCCSUS), U4.32 (VCC), U4.38 (VCCU), U4.44 (VCCU), U4.55 (VCCP), U4.62 (VCCP), U12.1 (VIN), U12.2 (VIN), U12.3 (VIN), U12.4 (EN), U12.15 (VIN), U12.16 (VIN); also elsewhere on the board
7.PCIE_NRESET: R69.1, U4.30 (!PERST); also elsewhere on the board
!INT: U4.2 (!SMI)
!PCIE_WAKE: U4.25 (!PEWAKE)
!RST$: R70.1, U4.9 (!PORST)
!SPI_CS$: U4.7 (!SPI_CS)
!USB1_NOC: U4.28 (!OC1)
!USB2_NOC: U4.29 (!OC2)
GND: C73.2, C74.2, C75.2, C76.2, C77.2, C78.2, C79.2, C82.2, C83.2, C84.2, C85.2, C86.2, C88.2, C89.2, C90.2, C91.2, C94.2, C158.2, C167.2, R11.1, U4.15 (GND), U4.65 (GND), U4.EPAD1 (GND), U4.EPAD2 (GND), U4.EPAD3 (GND), U4.EPAD4 (GND), U4.EPAD5 (GND), U4.EPAD6 (GND), U4.EPAD7 (GND), U4.EPAD8 (GND), U4.EPAD9 (GND), U4.EPAD10 (GND), U4.EPAD11 (GND), U4.EPAD12 (GND), U12.6 (GND), U12.EP (GND), U12.EP1 (GND), U12.EP2 (GND), U12.EP3 (GND), U12.EP4 (GND), Y5.2, Y5.4; also elsewhere on the board
PCIE_CLK_N: U4.49 (PCIE_REFCLK_N); also elsewhere on the board
PCIE_CLK_P: U4.48 (PCIE_REFCLK_P); also elsewhere on the board
PCIE_RX0__N: C93.2, U4.57 (PCIE_TX0_N)
PCIE_RX0__P: C92.2, U4.56 (PCIE_TX0_P)
PCIE_RX_N: C92.1; also elsewhere on the board
PCIE_RX_P: C93.1; also elsewhere on the board
PCIE_TX_N: U4.53 (PCIE_RX0_P); also elsewhere on the board
PCIE_TX_P: U4.54 (PCIE_RX0_N); also elsewhere on the board
REXT$: R11.2, U4.59 (REXT)
SPI_CLK$: U4.5 (SPI_CLK)
SPI_DI$: U4.8 (SPI_DI)
SPI_DO$: U4.6 (SPI_DO)
UART_RX$: U4.10 (UART_RX)
UART_TX$: U4.11 (UART_TX)
USB1_N: U4.22 (USB1_N); also elsewhere on the board
USB1_P: U4.23 (USB1_P); also elsewhere on the board
USB1_PWREN: U4.26 (PWRON1)
USB1_SSRX_N: U4.46 (USB1_SSRX_N); also elsewhere on the board
USB1_SSRX_P: U4.45 (USB1_SSRX_P); also elsewhere on the board
USB1_SSTX_N: U4.43 (USB1_SSTX_N); also elsewhere on the board
USB1_SSTX_P: U4.42 (USB1_SSTX_P); also elsewhere on the board
USB2_N: U4.18 (USB2_N)
USB2_P: U4.19 (USB2_P)
USB2_PWREN: U4.27 (PWRON2)
USB2_SSRX_N: U4.37 (USB2_SSRX_N)
USB2_SSRX_P: U4.36 (USB2_SSRX_P)
USB2_SSTX_N: U4.40 (USB2_SSTX_N)
USB2_SSTX_P: U4.39 (USB2_SSTX_P)
V1.2$: C74.1, C75.1, C78.1, C79.1, C82.1, C83.1, C84.1, C89.1, C90.1, C91.1, C167.1, U4.1 (VDD), U4.12 (VDD), U4.21 (VDDSUS), U4.33 (VDD), U4.34 (VDDSUS), U4.35 (VDDU), U4.41 (VDDU), U4.47 (VDDU), U4.52 (VDDP), U4.58 (VDDP), U12.9 (SENSE), U12.10 (VOUT), U12.11 (VOUT), U12.12 (VOUT), U12.13 (VOUT), U12.14 (VOUT)
VCC1V1_SS$: C94.1, U12.7 (SS)
XI$: C32.2, U4.51 (XI), Y5.1
XO$: C32.1, U4.50 (XO), Y5.3

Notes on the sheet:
PCIe to USB3.0

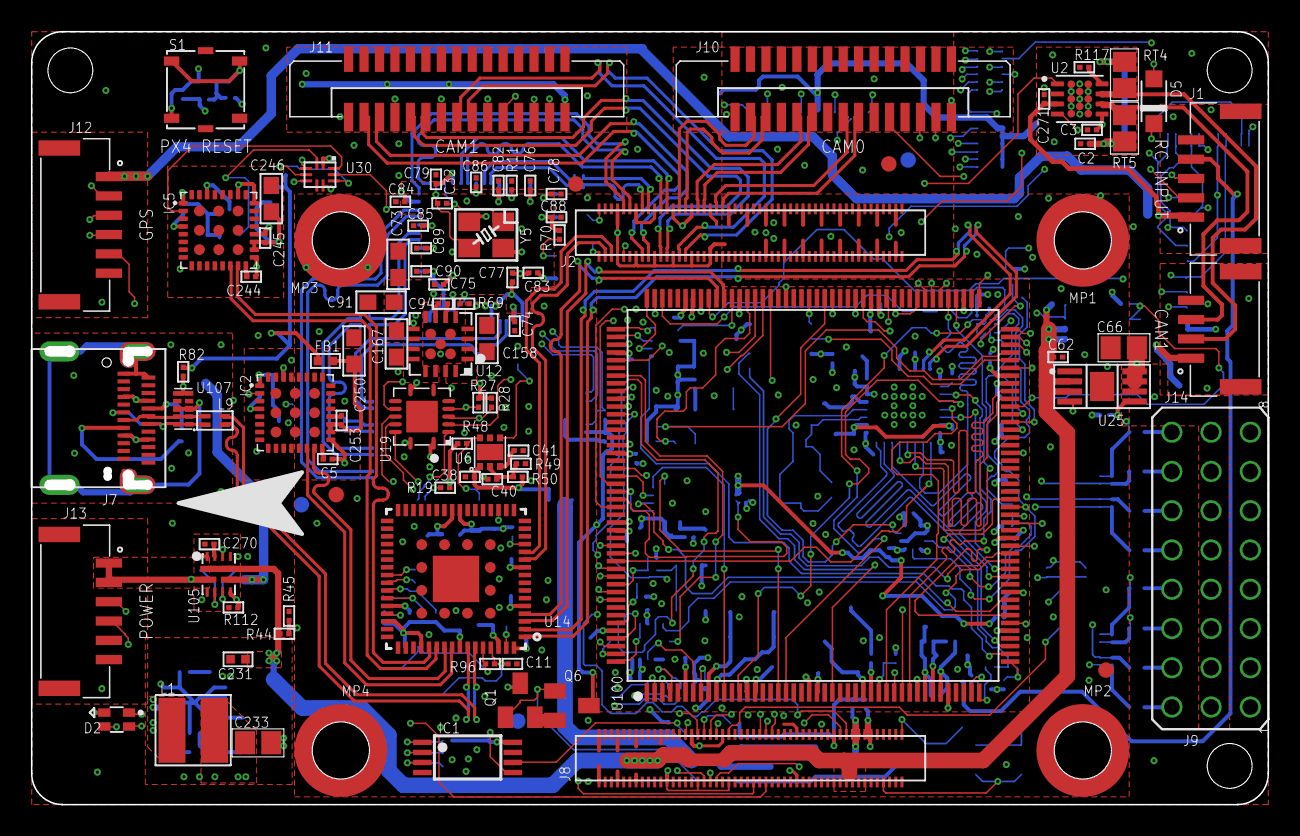
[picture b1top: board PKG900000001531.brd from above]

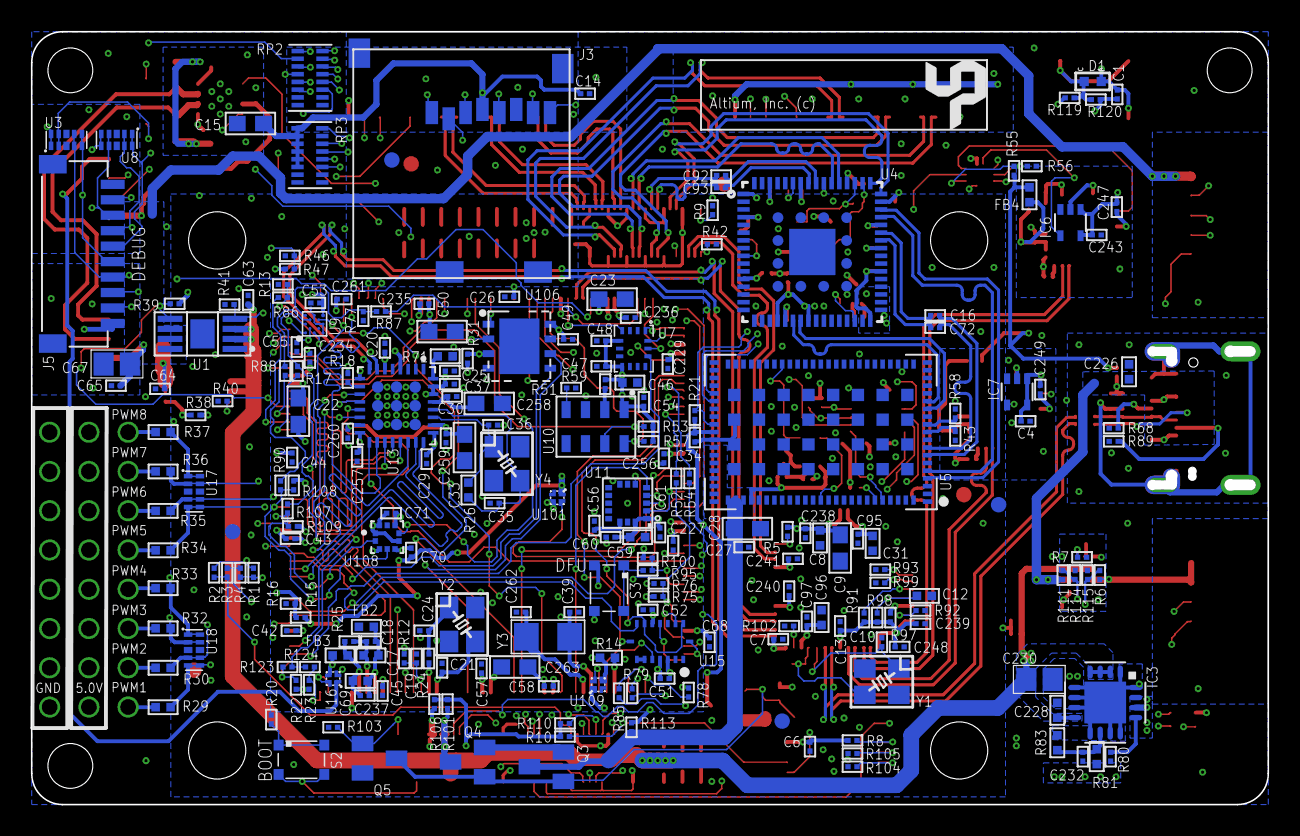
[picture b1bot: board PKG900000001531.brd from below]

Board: 6 copper layers, 80.0 x 50.0 mm, 326 parts (228 on the bottom side), 283 nets.

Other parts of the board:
U$53, U$55, U$60: DNP; GEPPETTO_HOLE_2.9

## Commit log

2020-10-13 Add README content, spec sheet, autodoc and folders
2020-10-14 Fixed copy-paste error in readme
2020-10-15 add links to brd and sch
2020-10-16 Product rebranding prior to release
2020-10-18 Added hardware documents for revision 1.
2020-10-19 Update firmware image to Ubuntu 20.04 CM4 image.
2020-11-23 Update firmware.md
    Add image username and password information.
2020-12-01 Update hardware files for revision 2.
2021-04-15 Update firmware to use upstream Raspberry Pi OS images and outline changes necessary to use cameras and onboard telemetry.
2021-05-27 Update board design files to v4.
    Add ROS2 and Coral support information to the firmware docs.
